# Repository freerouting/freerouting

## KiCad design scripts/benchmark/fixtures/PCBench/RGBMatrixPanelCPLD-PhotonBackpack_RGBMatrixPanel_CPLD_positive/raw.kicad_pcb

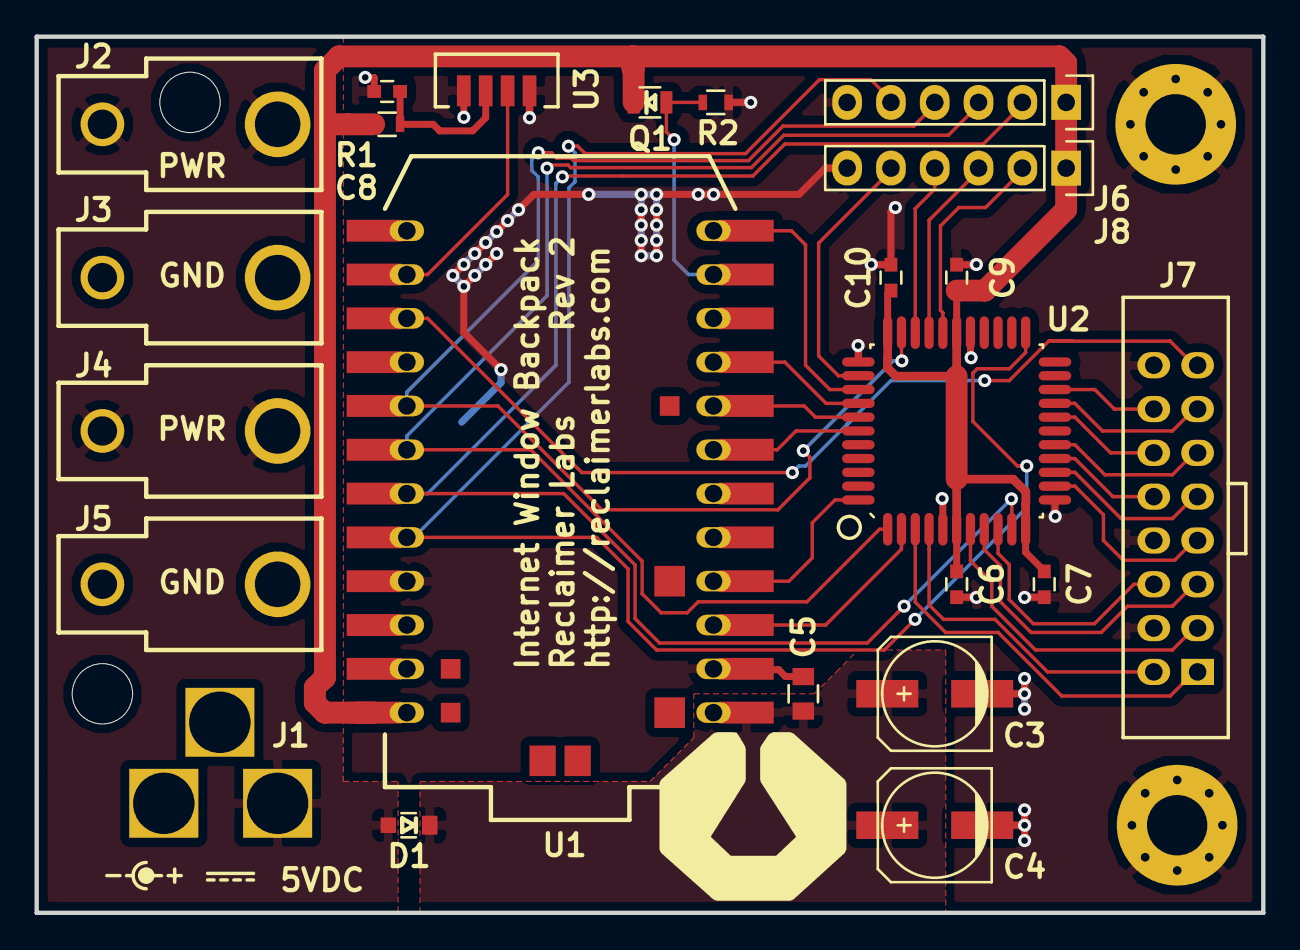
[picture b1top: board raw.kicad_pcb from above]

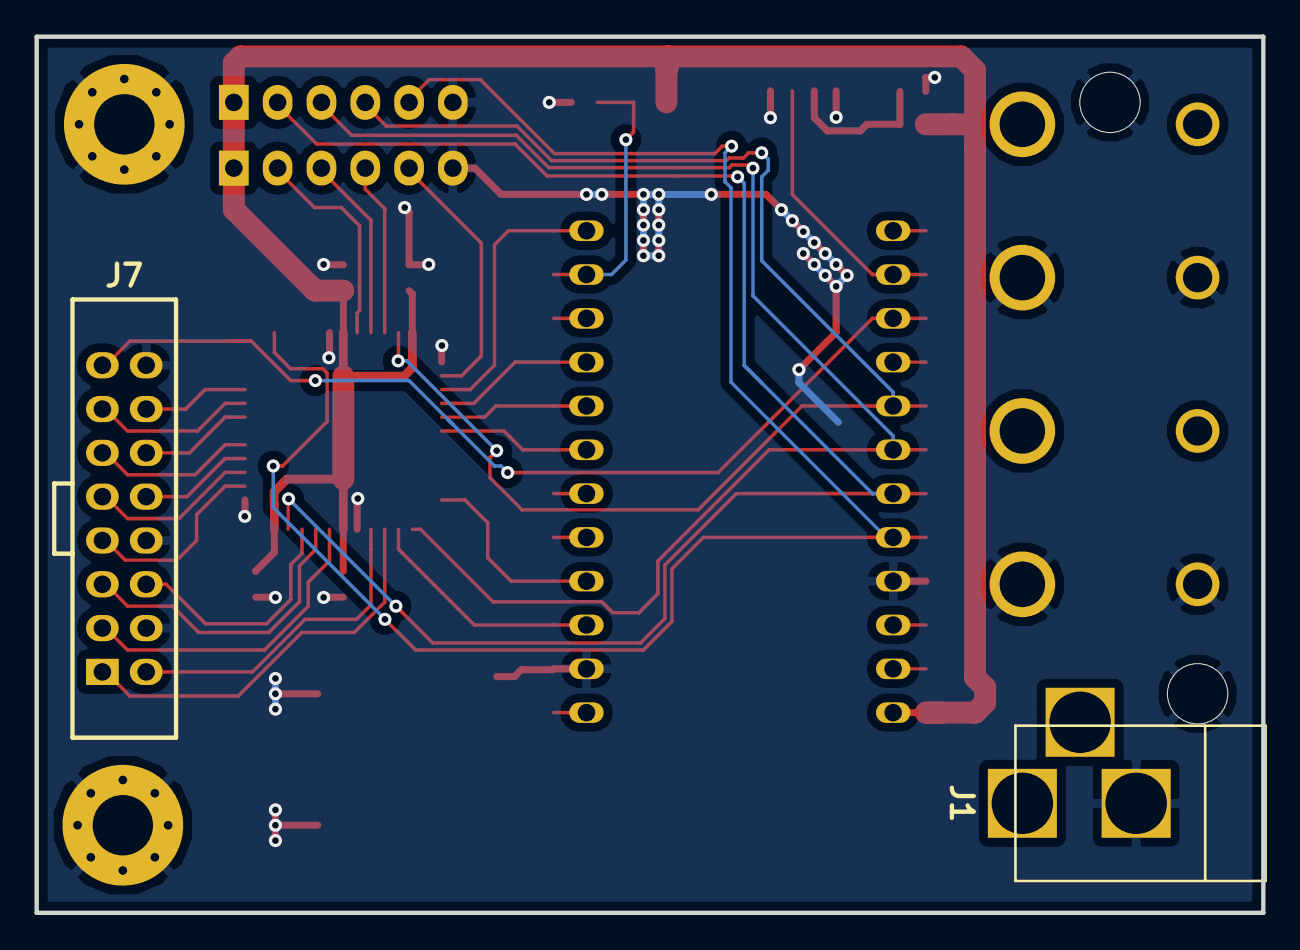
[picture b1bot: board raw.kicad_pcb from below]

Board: 2 copper layers, 71.1 x 50.8 mm, 27 parts (2 on the bottom side), 34 nets.

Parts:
C3, C4: 100uF; c_elec_6.3x5.7
C5: 10uF; C_0805
C6, C7, C8, C9, C10: 0.1uF; C_0603
D1: D_Schottky; SMini2-F5-B
J1: BARREL_JACK; BARREL_JACK_MPD_EJ508A
J2, J3, J4, J5: CONN_01X01; 3547
J6, J8: CONN_01X06; Socket_Strip_Straight_1x06
J7: CONN_02X08; HEADER_THRU_02x08_POL
Q1: Photo_Trans; Photo_Trans_0805
R1: 100R; R_0603
R2: 10k; R_0603
U1: PHOTON
U2: LC4032V-44TQFP; QFP_44
U3: TSOP75238TT
X1, X2: MTHOLE; MountingHole_3.5mm
X3, X4: MTHOLE; MountingHole_3.5mm_Pad_Via

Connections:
+3V3: C6.1, C7.1, C9.1, C10.1, J6.1, J8.1, Q1.C, R1.1, U1.24, U2.6, U2.11, U2.28, U2.33
+5V: D1.2, J1.1, J2.1, J4.1
+5VA: C3.1, C4.1, C5.1, D1.1, U1.1
/A: J7.9, U2.14
/B: J7.10, U2.15
/B1: J7.3, U2.7
/B2: J7.7, U2.13
/C: J7.11, U2.16
/CLK: J7.13, U2.19
/CPLD_B8: J8.2, U2.29
/CPLD_B9: J8.3, U2.30
/CPLD_B10: J8.4, U2.31
/CPLD_B12: J8.5, U2.35
/D: J7.12, U2.18
/G1: J7.2, U2.4
/G2: J7.6, U2.9
/IRDA: U1.14, U3.3
/LAT: J7.14, U2.20
/OE: J7.15, U1.15
/PHOTO: Q1.E, R2.1, U1.11
/R1: J7.1, U2.3
/R2: J7.5, U2.8
/RST_CPLD: U1.12, U2.36
/SPI_MISO: U1.8, U2.38
/SPI_MOSI: U1.7, U2.39
/SPI_SCK: U1.9, U2.37
/TCK: J6.2, U1.19, U2.10
/TDI: J6.3, U1.18, U2.1
/TDO: J6.4, U1.17, U2.32
/TMS: J6.5, U1.20, U2.23
/UART_RX: U1.4, U2.44
/UART_TX: U1.3, U2.2
GND: C3.2, C4.2, C5.2, C6.2, C7.2, C8.2, C9.2, C10.2, J1.2, J3.1, J5.1, J6.6, J7.4, J7.8, J7.16, J8.6, R2.2, U1.2, U1.21, U2.5, U2.12, U2.27, U2.34, U3.1, U3.4, X1.1, X2.1, X3.1, X4.1
unnamed: C8.1, R1.2, U3.2

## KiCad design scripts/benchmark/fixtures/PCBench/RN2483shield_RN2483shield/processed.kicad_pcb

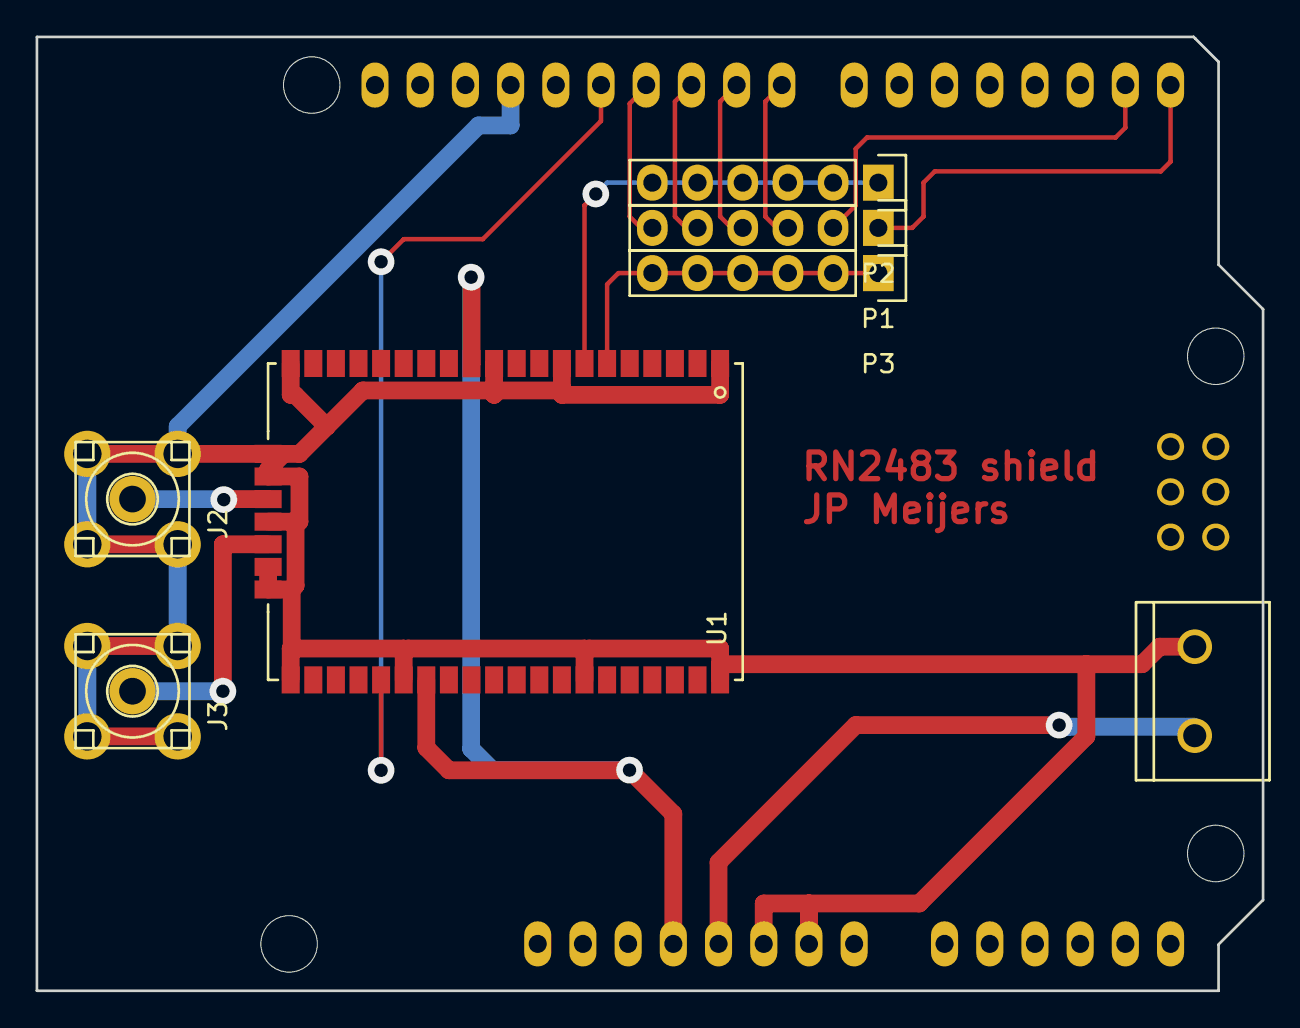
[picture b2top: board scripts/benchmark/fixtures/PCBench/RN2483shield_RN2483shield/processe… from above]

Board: 2 copper layers, 68.9 x 53.6 mm, 8 parts (0 on the bottom side), 14 nets.

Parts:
J1: SCREW_TERMINAL; SCREWTERMINAL-5MM-2
J2, J3: SMA; SMA_BOARD_UPRIGHT
P1, P2, P3: CONN_01X06; Socket_Strip_Straight_1x06
SHIELD1: ARDUINO_SHIELD
U1: RN2483

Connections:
3.3VOLT: SHIELD1.3V3, U1.12, U1.34
/AD_P8: P1.3, SHIELD1.8
/AD_P9: P1.4, SHIELD1.9
/AD_P10: P1.5, SHIELD1.10
/AD_P11: P1.6, SHIELD1.11
/HW_RX: P1.1, SHIELD1.0
/HW_TX: P1.2, SHIELD1.1
BATTERY: J1.2, SHIELD1.5V
GND: J1.1, J2.2, J2.3, J2.4, J2.5, J3.2, J3.3, J3.4, J3.5, SHIELD1.GND1, SHIELD1.GND2, SHIELD1.GND3, U1.1, U1.8, U1.11, U1.20, U1.21, U1.22, U1.24, U1.26, U1.27, U1.28, U1.33, U1.41, U1.47
unnamed: J2.1, U1.23
unnamed: J3.1, U1.25
RN_RESET: SHIELD1.12, U1.32
UART_ARDUINO_TO_RADIO: P2.1, P2.2, P2.3, P2.4, P2.5, P2.6, U1.7
UART_RADIO_TO_ARDUINO: P3.1, P3.2, P3.3, P3.4, P3.5, P3.6, U1.6

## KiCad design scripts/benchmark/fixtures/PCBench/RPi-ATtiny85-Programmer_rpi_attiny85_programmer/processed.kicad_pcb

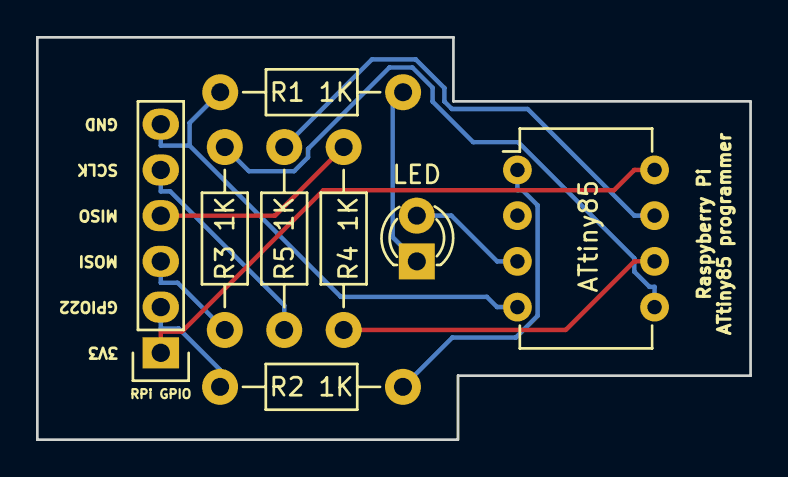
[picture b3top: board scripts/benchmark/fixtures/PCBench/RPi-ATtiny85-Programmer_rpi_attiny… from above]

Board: 2 copper layers, 39.6 x 22.4 mm, 9 parts (1 on the bottom side), 12 nets.

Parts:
ATtiny85: ATtiny85; DIP-8_W7.62mm
LED: LED; LED-3MM
R1 1K, R2 1K, R3 1K, R4 1K, R5 1K: 1K; Resistor_Horizontal_RM10mm
RPi GPIO: RPi_GPIO_SPI; Socket_Strip_Straight_1x06
_: Symbol_GNU-Logo_SilkscreenTop

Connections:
unnamed: ATtiny85.1, R2 1K.1
unnamed: ATtiny85.3, LED.2
unnamed: ATtiny85.4, R1 1K.2, RPi GPIO.6
unnamed: ATtiny85.5, R3 1K.2
unnamed: ATtiny85.6, R4 1K.2
unnamed: ATtiny85.7, R5 1K.2
unnamed: ATtiny85.8, RPi GPIO.1
unnamed: LED.1, R1 1K.1
unnamed: R2 1K.2, RPi GPIO.2
unnamed: R3 1K.1, RPi GPIO.3
unnamed: R4 1K.1, RPi GPIO.4
unnamed: R5 1K.1, RPi GPIO.5
